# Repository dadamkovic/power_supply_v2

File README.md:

The project files include routed 4 layer PCB board for a cassette intended to be used either standalone or
as part of a tower rack. The battery module includes:
- 4 lithium cells
- battery charge management
- overcurrent protection
- USB C PD negotiation
- cell balancing
- D-SUB interface

HW layout is production ready. SW includes skeleton generated using STM32 CubeMx.
Product visualization:<br>

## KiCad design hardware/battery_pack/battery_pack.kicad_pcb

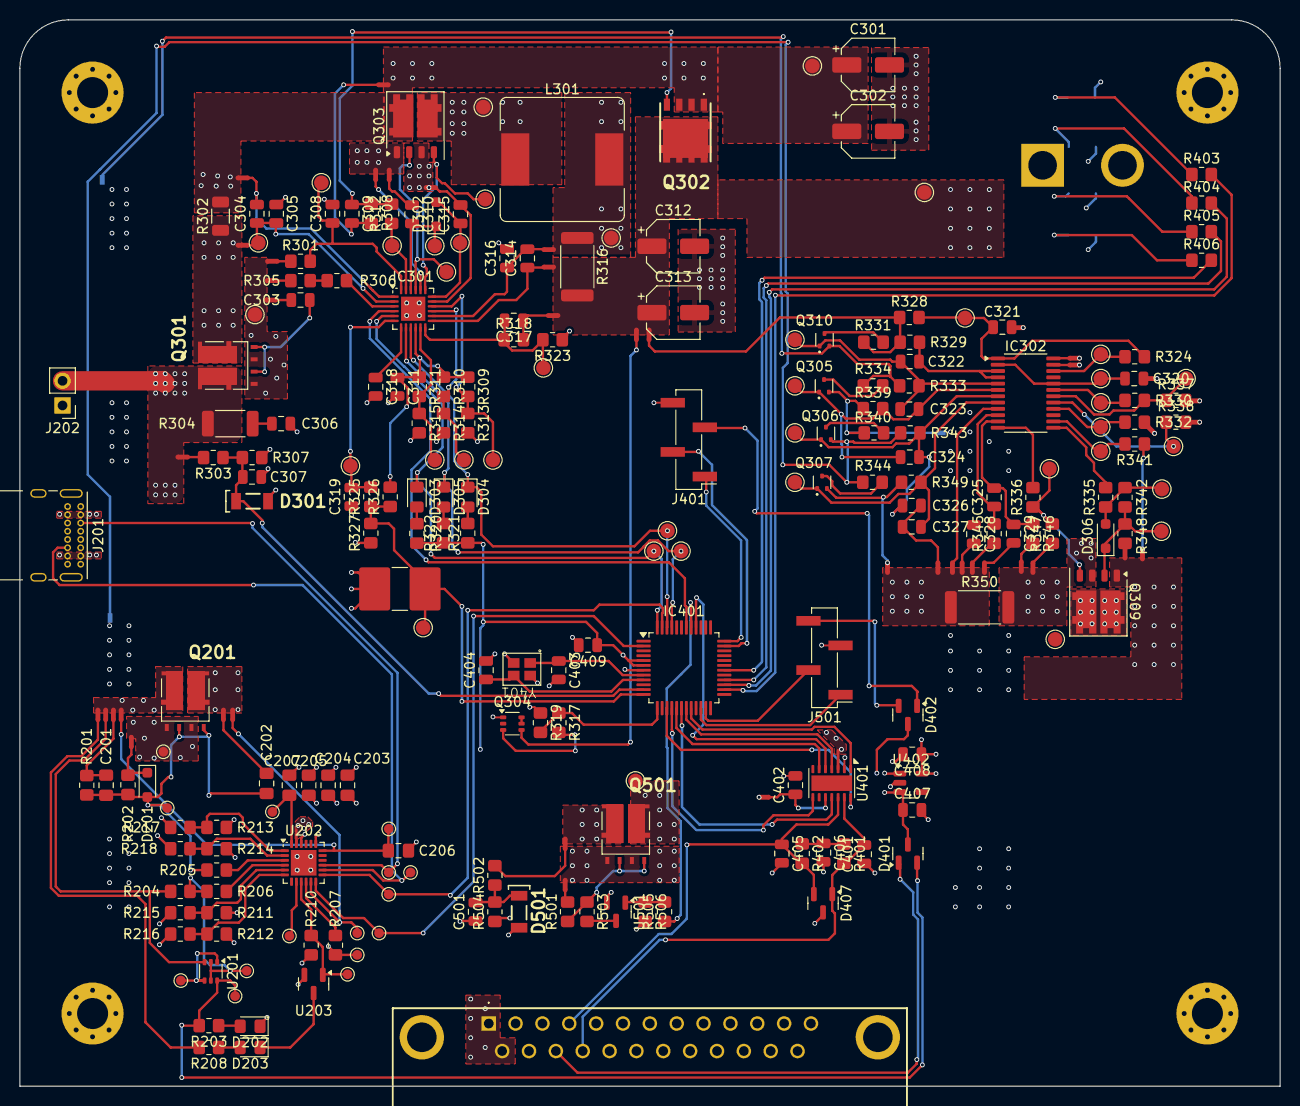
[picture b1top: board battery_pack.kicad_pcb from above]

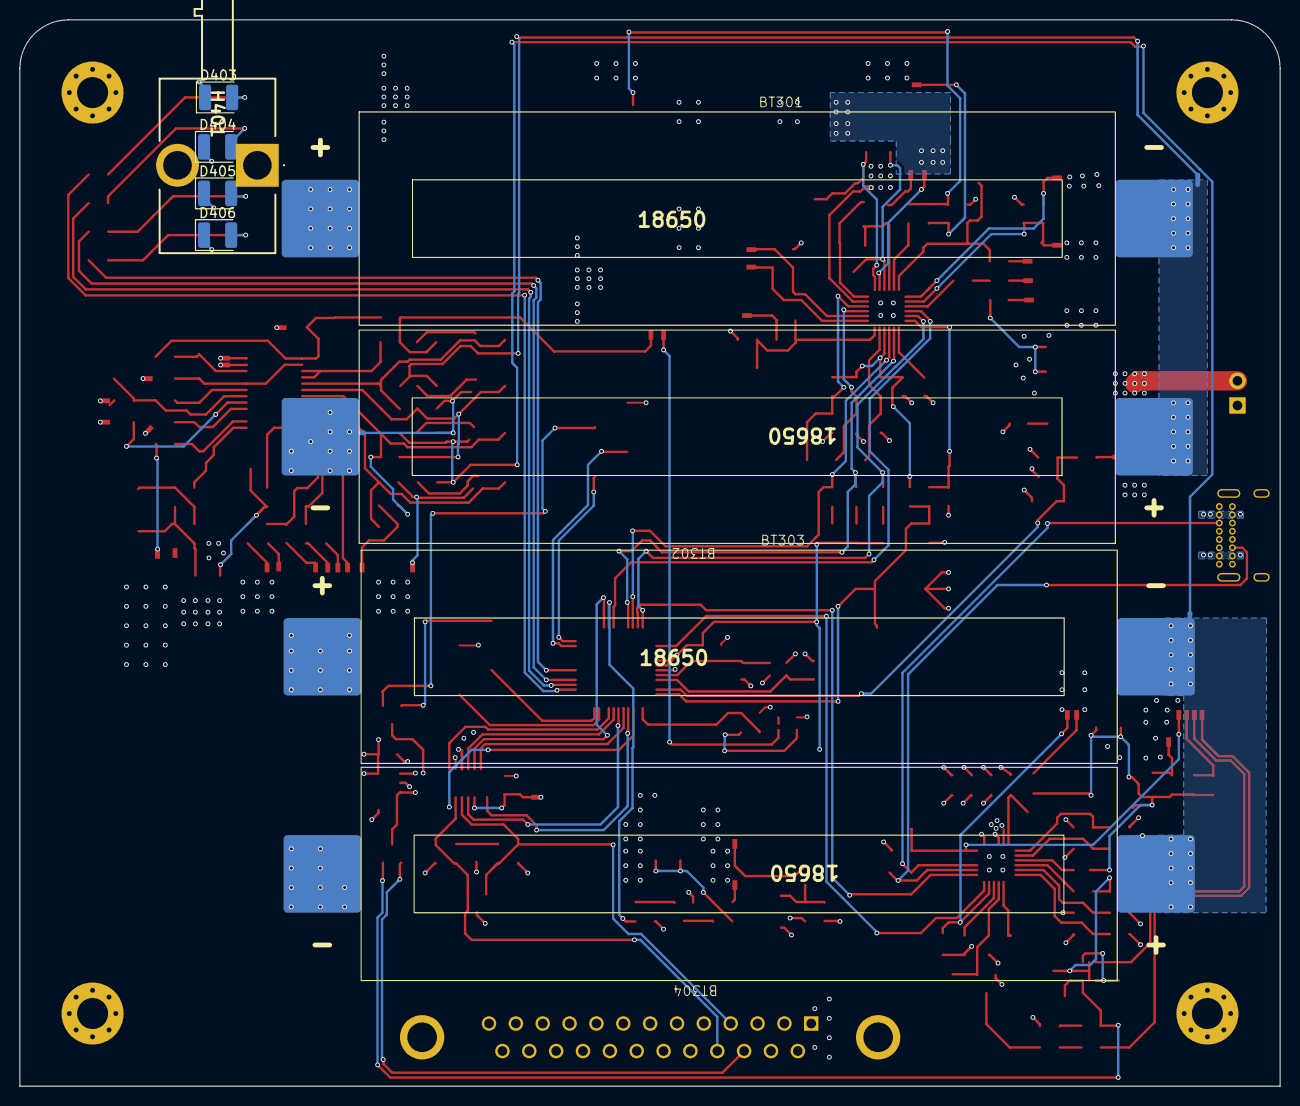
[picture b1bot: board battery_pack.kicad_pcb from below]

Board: 4 copper layers, 130.0 x 110.0 mm, 277 parts (12 on the bottom side), 172 nets.

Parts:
BT301, BT302, BT303, BT304: BAT; Battery_18650
C201, C202, C203, C207: 1u; C_0805_2012Metric_Pad1.18x1.45mm_HandSolder
C204, C205: 0.1u; C_0805_2012Metric_Pad1.18x1.45mm_HandSolder
C206: 3.3u; C_0805_2012Metric_Pad1.18x1.45mm_HandSolder
C301: 5u; CP_Elec_5x5.3
C302, C312, C313: 10u; CP_Elec_5x5.3
C303, C304, C305, C307, C309, C310, C314, C316, C319, C322, C323, C324, C325, C326, C327, C328, C329, C402, C407, C409, C501: 0.1u; C_0805_2012Metric
C306: 2.2u; C_0805_2012Metric
C308, C311, C315, C320, C321, C408: 1u; C_0805_2012Metric
C317: 22p; C_0805_2012Metric
C318: 64n; C_0805_2012Metric
C401, C405: 100p; C_0805_2012Metric
C403, C404: 10p; C_0805_2012Metric
C406: 4.7n; C_0805_2012Metric
D201, D302, D306: BAT54WS; D_SOD-323_HandSoldering
D202, D203: LED; LED_0805_2012Metric_Pad1.15x1.40mm_HandSolder
D301, D501: BZV55-B3V9; SOD80C
D303: LED_Y; LED_0805_2012Metric_Pad1.15x1.40mm_HandSolder
D304: LED_G; LED_0805_2012Metric_Pad1.15x1.40mm_HandSolder
D305: LED_R; LED_0805_2012Metric_Pad1.15x1.40mm_HandSolder
D401, D402: BAT54C; SOT-23
D403, D404, D405, D406: LED; LED_1210_3225Metric
D407: ESDCAN01-2BLY; SOT-23
H401: LPF-S014331S; LPFS014331S
H501, H502, H503, H504: MountingHole_Pad; MountingHole_3.2mm_M3_Pad_Via
IC301: BQ24618RGER; VQFN-24-1EP_4x4mm_P0.5mm_EP2.5x2.5mm
IC302: BQ7791504; TSSOP-24_4.4x7.8mm_P0.65mm
IC401: STM32C092CCT6; LQFP-48_7x7mm_P0.5mm
J201: USB_C_Receptacle_USB2.0; USB_C_Receptacle_GCT_USB4085
J202: Conn_01x02_Male; PinHeader_1x02_P2.54mm_Vertical
J401: SW_CONN; PinHeader_1x04_P2.54mm_Vertical_SMD_Pin1Left
J501: UART CONN; PinHeader_1x04_P2.54mm_Vertical_SMD_Pin1Left
J502: DB25_Plug_MountingHoles; DB25PL25
L301: 6.8u; L_Bourns_SRR1260
NT1, NT2, NT201, NT203, NT205, NT206, NT207, NT208, NT209, NT301, NT302, NT303, NT304, NT305, NT306, NT307, NT308, NT309, NT310, NT311, NT312, NT313, NT315, NT316, NT317, NT318, NT321, NT323, NT324, NT326, NT327, NT328, NT330, NT331, NT332, NT333, NT334, NT335, NT336, NT337, NT340, NT341, NT401, NT501, NT502: NetTie_2; NetTie-2_SMD_Pad0.5mm
Q201, Q301, Q501: SQJ951EP; PowerPAK® SO-8L Dual
Q302: STL45P3LLH6; PowerFLAT 5x6
Q303, Q309: STL36DN6F7; ST_PowerFLAT-6L_5x6mm_P1.27mm
Q304: MUN5334DW1; SOT-363_SC-70-6
Q305, Q306, Q307, Q310: DMG1012T; SOT-523
R201, R215, R217, R324, R337, R506: 10k; R_0805_2012Metric_Pad1.20x1.40mm_HandSolder
R202, R204: 49.9k; R_0805_2012Metric_Pad1.20x1.40mm_HandSolder
R203, R208, R505: 2k; R_0805_2012Metric_Pad1.20x1.40mm_HandSolder
R205, R206, R306, R312, R328, R503: 1k; R_0805_2012Metric_Pad1.20x1.40mm_HandSolder
R207: 60k; R_0805_2012Metric_Pad1.20x1.40mm_HandSolder
R210, R303, R323, R502: 50k; R_0805_2012Metric_Pad1.20x1.40mm_HandSolder
R211, R212, R213, R216: 5.1k; R_0805_2012Metric_Pad1.20x1.40mm_HandSolder
R214: 0k; R_0805_2012Metric_Pad1.20x1.40mm_HandSolder
R218: N/A; R_0805_2012Metric_Pad1.20x1.40mm_HandSolder
R301: 10R; R_0805_2012Metric_Pad1.20x1.40mm_HandSolder
R302: 10mR; R_1206_3216Metric
R304: 2R; R_2010_5025Metric
R305, R308, R309, R310, R311, R501: 100k; R_0805_2012Metric_Pad1.20x1.40mm_HandSolder
R307, R504: 8.8k; R_0805_2012Metric_Pad1.20x1.40mm_HandSolder
R313: 32.4k; R_0805_2012Metric_Pad1.20x1.40mm_HandSolder
R314: 17.8k; R_0805_2012Metric_Pad1.20x1.40mm_HandSolder
R315: 22.2k; R_0805_2012Metric_Pad1.20x1.40mm_HandSolder
R316: 10mR; R_2512_6332Metric
R317, R319: R_Small_US; R_0805_2012Metric_Pad1.20x1.40mm_HandSolder
R318: 350k; R_0805_2012Metric_Pad1.20x1.40mm_HandSolder
R320, R321, R322: 330; R_0805_2012Metric_Pad1.20x1.40mm_HandSolder
R325, R345, R346: 100; R_0805_2012Metric_Pad1.20x1.40mm_HandSolder
R326: 9.31k; R_0805_2012Metric_Pad1.20x1.40mm_HandSolder
R327: 430k; R_0805_2012Metric_Pad1.20x1.40mm_HandSolder
R329, R333, R335, R339, R343, R349: 1K; R_0805_2012Metric_Pad1.20x1.40mm_HandSolder
R330: 10K; R_0805_2012Metric_Pad1.20x1.40mm_HandSolder
R331, R334, R340, R344: 50R; R_0805_2012Metric_Pad1.20x1.40mm_HandSolder
R332: 0R; R_0805_2012Metric_Pad1.20x1.40mm_HandSolder
R336: 4.5K; R_0805_2012Metric_Pad1.20x1.40mm_HandSolder
R338: 487K; R_0805_2012Metric_Pad1.20x1.40mm_HandSolder
R341: 450K; R_0805_2012Metric_Pad1.20x1.40mm_HandSolder
R342, R347: 1M; R_0805_2012Metric_Pad1.20x1.40mm_HandSolder
R348: 3M; R_0805_2012Metric_Pad1.20x1.40mm_HandSolder
R350: 10m; R_2512_6332Metric
R401, R402: 60R; R_0805_2012Metric_Pad1.20x1.40mm_HandSolder
R403, R404, R405, R406: 330R; R_0805_2012Metric_Pad1.20x1.40mm_HandSolder
TH301: 103AT; R_2816_7142Metric_Pad3.20x4.45mm_HandSolder
TP301, TP302, TP303, TP305, TP307, TP308, TP309, TP310, TP311, TP312, TP313, TP314, TP315, TP316, TP317, TP318, TP319, TP320, TP321, TP322, TP323, TP324, TP325, TP326, TP327, TP328, TP329, TP330, TP331, TP332, TP333, TP334, TP335, TP336, TP337, TP338, TP339, TP340: TestPoint_Pad_D1.5mm
TPe201, TPe202, TPe203, TPe204, TPe205, TPe206, TPe207, TPe208, TPe209, TPe210, TPe211, TPe212, TPe213, TPe214, TPe215: TestPoint; TestPoint_Pad_D1.0mm
U201: BSS84DW; SOT-363_SC-70-6
U202: CYPD3177; QFN-24-1EP_4x4mm_P0.5mm_EP2.65x2.65mm
U203, U501: T2N7002AK; SOT-23
U401: TCAN1164; VSON-14-1EP_3x4.45mm_P0.65mm_EP1.6x4.2mm
U402: TLV70033_SOT23-5; SOT-23-5
Y401: ECX_2236B (10pF); ECX-2236B

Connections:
/battery_management/ACSET: IC301.16 (ACSET), R309.2, R313.1, TP312.1
/battery_management/BAT12: BT301.2 (-), BT302.1 (+), NT321.2
/battery_management/BAT23: BT302.2 (-), BT303.1 (+), NT324.2
/battery_management/BAT34: BT303.2 (-), BT304.1 (+), NT328.2
/battery_management/ISET1: IC301.11 (ISET1), R311.2, R315.1, TP309.1
/battery_management/ISET2: IC301.15 (ISET2), R310.2, R314.1, TP311.1
/battery_management/VREF: C311.1, IC301.10 (VREF), R309.1, R310.1, R311.1, R326.2
/uc_stage/FDCAN_Rx: IC401.19 (PB0), U401.4 (RXD)
/uc_stage/FDCAN_Tx: IC401.20 (PB1), U401.1 (TXD)
/uc_stage/OSC_X1: C403.1, IC401.8 (PF0-OSC_IN), Y401.1
/uc_stage/OSC_X2: C404.1, IC401.9 (PF1-OSC_OUT), Y401.3
/uc_stage/SPI1_MISO: IC401.17 (PA6), U401.6 (SD0/MISO)
/uc_stage/SPI1_MOSI: IC401.18 (PA7), U401.11 (SDI/MOSI)
/uc_stage/SPI1_SCK: IC401.16 (PA5), U401.8 (SCLK)
/uc_stage/SPI1_nCS: IC401.15 (PA4), U401.14 (nCS)
/uc_stage/SWCLK: IC401.36 (PA14-BOOT0), J401.1
/uc_stage/SWDIO: IC401.35 (PA13), J401.2
/uc_stage/SW_5V: D402.1, J401.3
/uc_stage/TCAN_nRST: IC401.40 (PD2), U401.5 (nRST)
/uc_stage/digLED1_Red_EN: IC401.26 (PB14), R403.2
/uc_stage/digLED2_Orange_EN: IC401.27 (PB15), R404.2
/uc_stage/digLED3_Green_EN: IC401.28 (PA8), R405.2
/uc_stage/digLED4_Green_EN: IC401.30 (PC6), R406.2
/usb_input/CC1: J201.A5 (CC1), TPe209.1, U202.15 (CC1)
/usb_input/CC2: J201.B5 (CC2), TPe210.1, U202.14 (CC2)
/usb_input/USB_Isolation_Common: NT203.2, Q201.1, Q201.3, TPe201.1
/usb_input/VCCD_1V8: C207.1, TPe214.1, U202.24 (VCCD)
/usb_input/VDDD_3V3: C203.1, C204.1, C205.1, R207.1, R211.1, R212.1, R213.1, R214.1, TPe205.1, U202.23 (VDDD)
CAN_H: C401.2, D407.1 (A1), J502.17, R401.2, U401.13 (CANH)
CAN_L: C405.1, D407.2 (A2), J502.4, R402.2, U401.12 (CANL)
EXT_5V: D401.1, J502.16
Earth: BT304.2 (-), NT1.2, NT2.1, NT316.1, NT318.2, NT323.2, NT326.2, NT327.2, NT330.1, NT331.2, NT332.2, NT333.2, NT340.2, NT341.2, R350.1
HPI_SCL: IC401.47 (PB8), TPe208.1, U202.13 (HPI_SCL)
HPI_SDA: IC401.2 (PC14-OSCX_IN), TPe211.1, U202.12 (HPI_SDA)
unnamed: C201.1, NT201.1, R201.1
unnamed: C202.1, NT205.1
unnamed: C303.1, NT304.1
unnamed: C303.2, Q301.2, Q301.4, R305.1, R306.1
unnamed: C306.1, R304.1
unnamed: C309.2, NT307.2, R308.2
unnamed: C310.1, NT309.2
unnamed: C317.1, NT313.1, R318.2
unnamed: C320.1, NT316.2
unnamed: C321.1, NT2.2
unnamed: C326.2, C327.1, NT330.2
unnamed: C328.2, NT340.1
unnamed: C329.2, NT341.1
unnamed: C406.1, R401.1, R402.1
unnamed: C201.2, C202.2, D201.2 (A), Q201.2, Q201.4, R201.2, R202.2, R205.1, TPe202.1
unnamed: D201.1 (K), NT203.1, R202.1
unnamed: D202.2 (A), R203.1
unnamed: D203.2 (A), R208.1
unnamed: D203.1 (K), U203.3
unnamed: C315.1, D302.2 (A), IC301.18 (REGN), TP317.1
unnamed: C310.2, D302.1 (K), IC301.22 (BTST), TP313.1
unnamed: D303.2 (A), R320.2
unnamed: D304.2 (A), R321.2
unnamed: D305.2 (A), R322.2
unnamed: D306.2 (A), R335.1, R342.2, TP334.1
unnamed: D306.1 (K), Q309.2, R342.1, R348.2, TP337.1
unnamed: D403.2 (A), R403.1
unnamed: D404.2 (A), R404.1
unnamed: D405.2 (A), R405.1
unnamed: D406.2 (A), R406.1
unnamed: C304.2, IC301.1 (ACN), NT306.1
unnamed: C304.1, C305.2, IC301.2 (ACP), NT305.1, TP307.1
unnamed: C315.2, IC301.17 (GND), NT315.2
unnamed: IC301.21 (HIDRV), Q303.2, TP310.1
unnamed: IC301.19 (LODRV), Q303.4, TP319.1
unnamed: IC301.20 (PH), NT308.2
unnamed: C314.1, IC301.13 (SRN), NT312.1
unnamed: C314.2, C316.1, IC301.14 (SRP), NT311.1
unnamed: C319.2, IC301.6 (TS), R325.2, TP323.1
unnamed: C318.1, IC301.7 (TTC)
unnamed: C308.1, IC301.24 (VCC), R301.2, TP301.1
unnamed: C317.2, IC301.12 (VFB), R318.1, R323.2, TP322.1
unnamed: IC301.3 (~ACDRV), R306.2
unnamed: IC301.23 (~BATDRV), R312.1, TP308.1
unnamed: C320.2, IC302.2 (AVDD), IC302.20 (CCFG), TP324.1
unnamed: IC302.16 (CBI), R332.1, TP330.1
unnamed: IC302.13 (CHG), R335.2
unnamed: IC302.23 (CTRC), NT1.1
unnamed: IC302.24 (CTRD), NT318.1
unnamed: IC302.12 (DSG), R336.2
unnamed: IC302.14 (LD), R341.2, TP332.1
unnamed: IC302.17 (OCDP), R338.1, TP331.1
unnamed: C325.2, C329.1, IC302.11 (SRN), R346.1
unnamed: C325.1, C328.1, IC302.10 (SRP), R345.2
unnamed: IC302.18 (TS), R330.2, R337.1, TP328.1
unnamed: C327.2, IC302.8 (VC0), Q307.1 (G), R349.2, TP338.1
unnamed: C324.2, C326.1, IC302.7 (VC1), Q306.1 (G), R343.2, TP335.1
unnamed: C323.2, C324.1, IC302.6 (VC2), Q305.1 (G), R339.2, TP333.1
unnamed: C322.2, C323.1, IC302.5 (VC3), Q310.1 (G), R333.2, TP329.1
unnamed: C322.1, IC302.3 (VC5), IC302.4 (VC4), R329.2
unnamed: C321.2, IC302.1 (VDD), R324.2, R328.2, TP326.1
unnamed: IC302.9 (VSS), NT332.1
unnamed: IC302.19 (VTB), R330.1, TP327.1
unnamed: L301.1, NT308.1, NT309.1, Q303.1, Q303.5, TP316.1
unnamed: L301.2, NT311.2, R316.1, TP314.1
unnamed: NT206.2, R204.1, U201.3
unnamed: NT209.2, R208.2
unnamed: NT301.1, NT303.2, NT304.2, Q301.1, Q301.3, TP303.1
unnamed: NT301.2, R301.1
unnamed: NT302.1, R303.2
unnamed: NT303.1, R305.2
unnamed: NT305.2, Q301.5, R302.1
unnamed: NT317.1, R328.1, R329.1, R331.1
unnamed: NT323.1, R332.2
unnamed: NT326.1, R338.2
unnamed: NT327.1, R337.2
unnamed: NT333.1, R345.1
unnamed: NT334.1, R346.2
unnamed: NT334.2, NT335.2, Q309.3, R350.2
unnamed: NT335.1, R347.1
unnamed: NT336.1, R348.1
unnamed: NT337.1, R341.1
unnamed: NT501.2, R502.2
unnamed: NT502.1, Q501.1, Q501.3
unnamed: NT502.2, R501.2
unnamed: C309.1, Q302.4 (G), R308.1, R312.2
unnamed: Q304.5 (B1), Q304.6 (C2)
unnamed: Q304.3 (C1), R317.2
unnamed: NT310.1, Q304.4 (E1)
unnamed: Q305.3 (D), R334.2
unnamed: NT324.1, Q305.2 (S), R339.1, R340.1
unnamed: Q306.3 (D), R340.2
unnamed: NT328.1, Q306.2 (S), R343.1, R344.1
unnamed: Q307.3 (D), R344.2
unnamed: NT331.1, Q307.2 (S), R349.1
unnamed: Q309.4, R336.1, R347.2, TP336.1
unnamed: Q309.5, Q309.7, TP339.1
unnamed: Q310.3 (D), R331.2
unnamed: NT321.1, Q310.2 (S), R333.1, R334.1
unnamed: Q501.2, Q501.4, R501.1, R503.1
unnamed: R204.2, R206.1, TPe204.1, U201.2, U201.5
unnamed: R503.2, U501.3
unnamed: R505.2, R506.1, U501.1
unnamed: TPe203.1, U201.1, U201.4
unnamed: R210.2, TPe215.1, U202.9 (FAULT), U203.1
unnamed: R207.2, U202.10 (FLIP)
unnamed: TPe213.1, U202.8 (GPIO_1)
unnamed: R211.2, R215.1, U202.5 (ISNK_COARSE)
unnamed: R212.2, R216.1, U202.6 (ISNK_FINE)
unnamed: R206.2, U202.4 (SAFE_PWR_EN)
unnamed: R205.2, U202.3 (VBUS_FET_EN)
unnamed: C206.1, NT208.1, TPe206.1, U202.18 (VBUS_IN)
unnamed: R214.2, R218.1, U202.2 (VBUS_MAX)
unnamed: R213.2, R217.1, U202.1 (VBUS_MIN)
unnamed: NT207.2, TPe207.1, U202.11 (VDC_OUT)
unnamed: C407.1, D401.3, D402.3, U401.3 (VCCOUT), U402.1 (IN), U402.3 (EN)
unnamed: C402.1, NT401.1, U401.10 (VSUP)
PACK +: BT301.1 (+), C312.1, C313.1, NT310.2, NT312.2, NT313.2, NT317.2, Q302.5 (D), Q302.6 (D), Q302.7 (D), Q302.8 (D), R316.2, TP315.1
PACK -: C203.2, C204.2, C205.2, C206.2, C207.2, C301.2, C302.2, C305.1, C306.2, C307.1, C308.2, C311.2, C312.2, C313.2, C316.2, C318.2, C319.1, C401.1, C402.2, C403.2, C404.2, C405.2, C406.2, C407.2, C408.2, C409.2, C501.1, D202.1 (K), D301.2 (A), D403.1 (K), D404.1 (K), D405.1 (K), D406.1 (K), D407.3 (common), D501.2 (A), H501.1, H502.1, H503.1, H504.1, IC301.25 (EP), IC401.7 (VSS/VSSA), J201.A1 (GND), J201.A12 (GND), J201.B1 (GND), J201.B12 (GND), J201.S1 (SHIELD), J202.1, J401.4, J501.3, J502.0 (PAD), J502.2, J502.3, J502.12, J502.15, J502.24, NT315.1, NT336.2, NT337.2, Q303.3, Q304.1 (E2), Q309.1, R210.1, R215.2, R216.2, R217.2, R218.2, R307.1, R313.2, R314.2, R315.2, R319.1, R323.1, R327.1, R504.1, R506.2, TH301.2, U202.19 (GND), U202.22 (VSS), U202.25 (TP), U203.2, U401.2 (GND), U402.2 (GND), U501.2, Y401.2, Y401.4
UART3_Rx: IC401.23 (PB11), J501.2
UART3_Tx: IC401.22 (PB10), J501.1
UART_5V: D402.2, J501.4
USB_C_BUS: J201.A4 (VBUS), J201.A9 (VBUS), J201.B4 (VBUS), J201.B9 (VBUS), NT201.2, NT206.1, NT208.2, NT209.1, Q201.6
VREG_3V3: C408.1, C409.1, IC401.5 (VREF+), IC401.6 (VDD/VDDA), R320.1, R321.1, R322.1, U402.5 (OUT)
V_AUX: J502.1, J502.14, NT501.1, Q501.6
V_AUX_SUPPLY: J202.2, NT205.2, NT207.1, NT302.2, Q201.5, Q301.6, Q501.5, R304.2, TP302.1
V_SYSTEM: C301.1, C302.1, J502.13, J502.25, NT306.2, NT307.1, NT401.2, Q302.1 (S), Q302.2 (D), Q302.3 (D), Q303.7, R302.2, TP305.1
V_USB_SAFE: D401.2, R203.2, TPe212.1, U201.6
anBatteryMeas: IC401.13 (PA2), R317.1, R319.2
anThermistorSense: IC401.12 (PA1), R325.1, R326.1, R327.2, TH301.1, TP325.1
anUSBVoltage: C307.2, D301.1 (K), IC401.11 (PA0), R303.1, R307.2
digCharge_EN: IC301.4 (CE), IC401.42 (PB3)
digPgDIS: D305.1 (K), IC301.8 (~PG), IC401.45 (PB6), TP321.1
digSTAT1: D303.1 (K), IC301.5 (STAT1), IC401.48 (PB9), TP318.1
digSTAT2: D304.1 (K), IC301.9 (STAT2), IC401.46 (PB7), TP320.1
gAnAuxilaryVoltage: C501.2, D501.1 (K), R502.1, R504.2
gAuxilarySup_En: IC401.41 (PD3), R505.1
gDigPressEN: IC302.22 (PRES), R324.1, TP340.1

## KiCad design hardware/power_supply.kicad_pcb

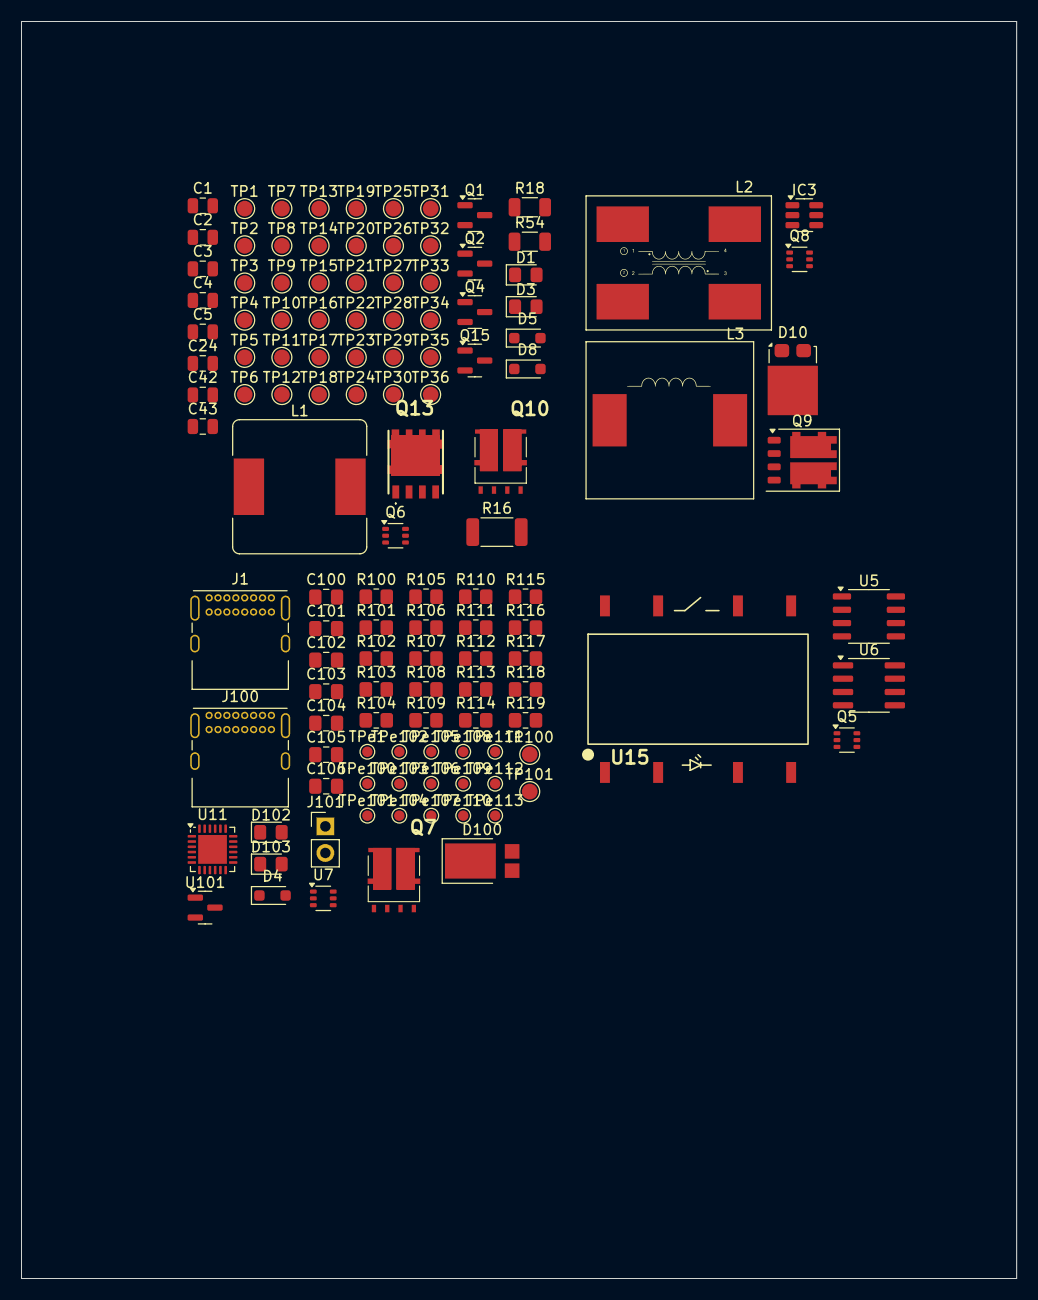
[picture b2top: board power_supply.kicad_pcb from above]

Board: 2 copper layers, 95.0 x 120.0 mm, 124 parts (0 on the bottom side), 58 nets, no tracks yet.

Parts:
C1, C2, C3, C4, C5, C24, C42, C43: 0.1u; C_0805_2012Metric
C100, C101, C102, C106: 1u; C_0805_2012Metric_Pad1.18x1.45mm_HandSolder
C103, C104: 0.1u; C_0805_2012Metric_Pad1.18x1.45mm_HandSolder
C105: 3.3u; C_0805_2012Metric_Pad1.18x1.45mm_HandSolder
D1: LED_Y; LED_0805_2012Metric_Pad1.15x1.40mm_HandSolder
D3: LED_R; LED_0805_2012Metric_Pad1.15x1.40mm_HandSolder
D4, D5, D8: BAT54WS; D_SOD-323_HandSoldering
D10: D_AAK; TO-277A
D100: SBR8M; D_PowerDI-5
D102, D103: LED; LED_0805_2012Metric_Pad1.15x1.40mm_HandSolder
IC3: UCC27531DBVR; SOT-23-6
J1, J100: USB_C_Receptacle_USB2.0; USB_C_Receptacle_GCT_USB4085
J101: Conn_01x02_Male; PinHeader_1x02_P2.54mm_Vertical
L1: 6.8u; L_Bourns_SRR1260
L2: 74485540101
L3: IHLP5050EZER4R7M5A; IHLP-5050EZ
Q1, Q2, Q4, Q15: 2N7002; SOT-23
Q5, Q6, Q8: MUN5334DW1; SOT-363_SC-70-6
Q7, Q10: SQJ951EP; PowerPAK® SO-8L Dual
Q9: STL120N8F7; ST_PowerFLAT-6L_5x6mm_P1.27mm
Q13: STL45P3LLH6; PowerFLAT 5x6
R16: 2R; R_2010_5025Metric
R18, R54: 10mR; R_1206_3216Metric
R100, R116, R118: 10k; R_0805_2012Metric_Pad1.20x1.40mm_HandSolder
R101, R103: 49.9k; R_0805_2012Metric_Pad1.20x1.40mm_HandSolder
R102, R109: 2k; R_0805_2012Metric_Pad1.20x1.40mm_HandSolder
R104, R105: 1k; R_0805_2012Metric_Pad1.20x1.40mm_HandSolder
R106, R107: 2.2k; R_0805_2012Metric_Pad1.20x1.40mm_HandSolder
R108: 60k; R_0805_2012Metric_Pad1.20x1.40mm_HandSolder
R110, R112, R113, R114, R117: 5.1k; R_0805_2012Metric_Pad1.20x1.40mm_HandSolder
R111: 50k; R_0805_2012Metric_Pad1.20x1.40mm_HandSolder
R115: 0k; R_0805_2012Metric_Pad1.20x1.40mm_HandSolder
R119: N/A; R_0805_2012Metric_Pad1.20x1.40mm_HandSolder
TP1, TP2, TP3, TP4, TP5, TP6, TP7, TP8, TP9, TP10, TP11, TP12, TP13, TP14, TP15, TP16, TP17, TP18, TP19, TP20, TP21, TP22, TP23, TP24, TP25, TP26, TP27, TP28, TP29, TP30, TP31, TP32, TP33, TP34, TP35, TP36: TestPoint_Pad_D1.5mm
TP100, TP101: HPI_INT; TestPoint_Pad_D1.5mm
TPe1, TPe100, TPe101, TPe102, TPe103, TPe104, TPe105, TPe106, TPe107, TPe108, TPe109, TPe110, TPe111, TPe112, TPe113: TestPoint; TestPoint_Pad_D1.0mm
U5: TSB712; SO-8_3.9x4.9mm_P1.27mm
U6: TMCS1108; SOIC-8_3.9x4.9mm_P1.27mm
U7: BSS84DW; SOT-363_SC-70-6
U11: CYPD3177; QFN-24-1EP_4x4mm_P0.5mm_EP2.75x2.75mm
U15: CPC1907B
U101: T2N7002AK; SOT-23

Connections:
/usb_input/BACKUP_POWER: D100.2 (A), J101.2
/usb_input/CC1: J100.A5 (CC1), TPe108.1, U11.15 (CC1)
/usb_input/CC2: J100.B5 (CC2), TPe109.1, U11.14 (CC2)
/usb_input/VCCD_1V8: C106.1, TPe1.1, U11.24 (VCCD)
/usb_input/VDDD_3V3: C102.1, C103.1, C104.1, R108.1, R112.1, R113.1, R114.1, R115.1, TPe104.1, TPe111.1
Earth: C4.2, C5.1, C42.1, C42.2, C43.2, Q1.2 (S)
HPI_SCL: R107.2, TPe107.1, U11.13 (HPI_SCL)
HPI_SDA: R106.2, TPe110.1, U11.12 (HPI_SDA)
unnamed: Q10.1, Q10.3, TP1.1
unnamed: Q10.2, Q10.4
unnamed: L2.3, Q9.5 (D), Q9.7 (D)
unnamed: D10.1 (A), D10.2 (A), L2.1
unnamed: C100.2, C101.2, D4.2 (A), Q7.2, Q7.4, R100.2, R101.2, R104.1, TPe101.1
unnamed: D4.1 (K), Q7.1, Q7.3, R101.1, TPe100.1
unnamed: D5.2 (A), TP27.1
unnamed: D5.1 (K), TP29.1
unnamed: U15.7 (D2_1), U15.8 (D2_2)
unnamed: D8.2 (A), TP15.1
unnamed: D8.1 (K), TP6.1
unnamed: D10.3 (K), L3.1
unnamed: D102.2 (A), R102.1
unnamed: D103.2 (A), R109.1
unnamed: D103.1 (K), U101.3
unnamed: U6.1 (IN+), U6.2 (IN+)
unnamed: C5.2, Q1.1 (G), TP25.1
unnamed: C3.2, C4.1, Q2.1 (G), TP24.1
unnamed: C2.2, C3.1, Q4.1 (G), TP22.1
unnamed: C1.2, C2.1, Q15.1 (G), TP23.1
unnamed: Q10.5, R18.1, TP3.1
unnamed: L1.1, TP7.1
unnamed: L1.2, R54.1, TP8.1
unnamed: J1.A4 (VBUS), J1.A9 (VBUS), J1.B4 (VBUS), J1.B9 (VBUS)
unnamed: U15.5 (D1_1), U15.6 (D1_2)
unnamed: Q5.5 (B1), Q5.6 (C2)
unnamed: Q6.5 (B1), Q6.6 (C2)
unnamed: Q8.5 (B1), Q8.6 (C2)
unnamed: R103.2, R105.1, TPe103.1, U7.2, U7.5
unnamed: TPe102.1, U7.1, U7.4
unnamed: R111.2, TPe113.1, U11.9 (FAULT), U101.1
unnamed: R108.2, U11.10 (FLIP)
unnamed: TP101.1, U11.7 (HPI_INT)
unnamed: R112.2, R116.1, U11.5 (ISNK_COARSE)
unnamed: R113.2, R117.1, U11.6 (ISNK_FINE)
unnamed: R115.2, R119.1, U11.2 (VBUS_MAX)
unnamed: R114.2, R118.1, U11.1 (VBUS_MIN)
unnamed: U15.1 (N/C_1), U15.4 (N/C_2)
PACK +: Q6.4 (E1), Q13.5 (D), Q13.6 (D), Q13.8 (D), R54.2, TP9.1
PACK -: C102.2, C103.2, C104.2, C105.2, C106.2, D102.1 (K), IC3.4 (GND), J1.A1 (GND), J1.A12 (GND), J1.B1 (GND), J1.B12 (GND), J1.S1 (SHIELD), J100.A1 (GND), J100.A12 (GND), J100.B1 (GND), J100.B12 (GND), J100.S1 (SHIELD), J101.1, L2.4, Q5.1 (E2), Q6.1 (E2), Q8.1 (E2), Q9.1 (S), Q9.2 (S), Q9.3 (S), R110.2, R111.1, R116.2, R117.2, R118.2, R119.2, U5.4 (V-), U6.5 (GND), U11.19 (GND), U11.22 (VSS), U101.2
USB_C_BUS: C100.1, C105.1, J100.A4 (VBUS), J100.A9 (VBUS), J100.B4 (VBUS), J100.B9 (VBUS), Q7.6, R100.1, R103.1, R109.2, TPe105.1, U7.3, U11.18 (VBUS_IN)
USB_C_D+: J1.A6 (D+), J1.B6 (D+)
USB_C_D-: J1.A7 (D-), J1.B7 (D-)
USB_C_GPIO: R110.1, TPe112.1, U11.8 (GPIO_1)
VREG1_POWER: IC3.3 (VDD), L2.2
VREG2_POWER: L3.2, U5.8 (V+)
VREG_3V3: R106.1, R107.1
V_SYSTEM: Q13.1 (S), Q13.2 (D), Q13.3 (D), R18.2, TP2.1, TP11.1, TP12.1
V_USB_OUT: C101.1, D100.1 (K), Q7.5, Q10.6, R16.2, TP19.1, TPe106.1, U11.11 (VDC_OUT)
V_USB_SAFE: R102.2, TP100.1, U7.6

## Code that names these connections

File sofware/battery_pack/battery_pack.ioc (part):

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Mcu.Name=STM32C092CCTx
Mcu.Package=LQFP48
Mcu.UserName=STM32C092CCTx
PA0.Mode=IN0
PA0.Signal=ADC1_IN0
PA1.Mode=IN1
PA1.Signal=ADC1_IN1
PA13.Mode=Serial_Wire
PA13.Signal=DEBUG_SWDIO
PA14-BOOT0.Mode=Serial_Wire
PA14-BOOT0.Signal=DEBUG_SWCLK
PA2.Mode=IN2
PA2.Signal=ADC1_IN2
PA4.Signal=GPIO_Output
PA5.Mode=Full_Duplex_Master
PA5.Signal=SPI1_SCK
PA6.Mode=Full_Duplex_Master
PA6.Signal=SPI1_MISO
PA7.Mode=Full_Duplex_Master
PA7.Signal=SPI1_MOSI
PB0.GPIOParameters=GPIO_PuPd
PB0.GPIO_PuPd=GPIO_NOPULL
PB0.Mode=FDCAN_Activate
PB0.Signal=FDCAN1_RX
PB1.GPIOParameters=GPIO_PuPd
PB1.GPIO_PuPd=GPIO_NOPULL
PB1.Mode=FDCAN_Activate
PB1.Signal=FDCAN1_TX
PB10.Mode=Asynchronous
PB10.Signal=USART3_TX
PB11.Mode=Asynchronous
PB11.Signal=USART3_RX
PB3.Signal=GPIO_Input
PB4.Signal=GPIO_Input
PB5.Signal=GPIO_Input
PB6.Signal=GPIO_Input
PB7.Signal=GPIO_Input
PB8.Mode=I2C
PB8.Signal=I2C1_SCL
PB9.Signal=GPIO_Input
PC14-OSCX_IN(PC14).Mode=I2C
PC14-OSCX_IN(PC14).Signal=I2C1_SDA
PD2.Signal=GPIO_Input
PD3.Signal=GPIO_Input
PF0-OSC_IN(PF0).Mode=HSE-External-Oscillator
PF0-OSC_IN(PF0).Signal=RCC_OSC_IN
PF1-OSC_OUT(PF1).Mode=HSE-External-Oscillator
PF1-OSC_OUT(PF1).Signal=RCC_OSC_OUT
RCC.HSE_VALUE=48000000
RCC.SYSCLKFreq_VALUE=48000000
RCC.SYSCLKSource=RCC_SYSCLKSOURCE_HSE
board=custom

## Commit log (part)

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2024-09-06 Started work on the schematic.
2024-09-06 Rough schematic of battery charger.
2024-09-10 Rought draft of battery charger and started SEPIC stage
2024-09-14 Continued work on schematic.
2024-10-06 Component values chosen for bat. charge, bat. protect, USB input
2024-10-13 Most work finished on stage1. Moving on to stage2.
2025-04-21 More simulation and work done on SEPIC stage. MOSFET changes to USB stage and charging stage.
2025-05-10 Saving prior to changing project structure
2025-06-30 Started routing of battery pack.
2025-07-06 Finished routing. Finall review and re-annotation pending.
